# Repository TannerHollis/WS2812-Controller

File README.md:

# WS2812 Controller

 - WS2812 LED: [WS2812](https://cdn-shop.adafruit.com/datasheets/WS2812.pdf)
 - ICE40UL640: [ICE40UL640](https://www.latticesemi.com/~/media/LatticeSemi/Documents/DataSheets/iCE/iCE40UltraLiteDataSheetDS1050.pdf)

## WS2812 LED Controller
[WS2812](https://cdn-shop.adafruit.com/datasheets/WS2812.pdf) LEDs are common RGB LEDs found everywhere today. They are fundamentally controlled by a simple PWM input that signals a single bit in each period. By varying the pwm signal from either 33% duty cycle to 67% duty cycle, one bit after another, data is latched by a timing constraint as seen in the documents. The basic WS2812 RGB LED is shown below.

While in theory, this RGB LED seems practical enough to control. Many various CPU intensive schemes have been created to bit-bang their way to victory. Most methods involve the use of DMA and TIMers with large buffers in STM32 microcontrollers, while in Arduino the method used is usually direct port manipulation and bit-banging. Not to mention other tricks of the trade usually involve using Assembly, *Yuck!* Even with all of the advancements in microcontroller technology of today, it is over-encumbering for the small silicon we all love and play with. 

Ideally there should be little to no overhead in microcontrollers for the actual transmission of the data to the LEDs. Also, there should ideally be on-board storage that will store values of each pixel to offload memory constraints. Well, if you've been looking for something along these lines, then perhaps you should stop and take a look at this project.

## FPGA Based

After looking at the ["smallest FPGA" in the world](https://www.latticesemi.com/Products/FPGAandCPLD/iCE40Ultra), I was curious to check it out for myself. Indeed, it is very small at just 1.4mm x 1.4mm with only 16 pins. In fact, it gets worse at only 10 useable I/O's. But wait, 4 of the 10 I/O's are dedicated SPI port programming lines, leaving you with only 6 I/O's. Oh wait, don't forget that there is only *one* traditional push-pull output and the other 5 are open-drain outputs. The ICE40UL640 also has 640 LUTs (LookUp Tables), and although it's not a good measure to use for capacity in FPGAs, it is a good metric when compared to a basic FGPA like the [Intel Cyclone V-A2](https://www.intel.com/content/dam/www/programmable/us/en/pdfs/literature/hb/cyclone-v/cv_51001.pdf) which has 25,000 LUTs. 

One really great thing about the ICE40UL640 is the RAM included. There are 14 blocks of 512x8bit ram in this FPGA which are 100% utilized for memory. Users can utilize this memory however they want, whether it be for user-data or purely LED data. Each LED requires 24bits of data, which means there is a total capacity of 2389 LEDs in one WS2812 Driver. In fact, this device could be used as additional RAM, which is easy to interface using SPI. Albeit, not the fastest memory controller due to the method of SPI clock detection.

**Below is the Device Architecture**

## SPI 
The SPI module in this device runs off of the device's internal High Frequency Oscillator at 48 MHz. Common practices of SPI communication protocols in FPGAs use clock-domain crossing, which means the internal SPI module operates based on two clocks. Configurations like this tend to operate at higher speeds, but require more logic elements to synthesize. Since this device is so limited in total number of elements, this device uses a "buffer clock" design. Using a buffer of only two clock cycles means, that the effective SPI input clock frequency must be half of the device's operating frequency. For more stable operation, the maximum SPI clock frequency should be:

    f_clk_spi < 24MHz

However, to ensure more stable communications it is recommended to operate well below this frequency when possible.

### SPI Communication Protocol
This device uses 24 bit (3 byte) commands to operate the device, typically consisting of the following format:

    //n'bx = don't care of size n bits
    write =		{3'b100, addr[12:0], data[7:0]};
    read =		{3'b000, addr[12:0], 8'bx};
    clear_ram =	{3'b011, 21'bx};
    fill_ram =	{3'b101, 13'bx, data[7:0]};
    send_leds =	{3'b111, 8'bx, num_leds[12:0]};

There are only a few instructions required to operate this device:
|op|Binary|Hex|Parameter(s)|Description|
|--|--|--|--|--|
|write|100|0x80|addr, data|write data to address|
|read|000|0x00|addr|read data from address|
|clear_ram|011|0x60|N/A|clear ram with zeros|
|fill_ram|101|0xA0|data|fill ram with data|
|send_leds|111|0xE0|num_leds|send leds stopping at num_leds|

A shorthand way of declaring instructions in the c language psuedocode:

    uint8_t op = 0x80;	//write op
    uint16_t addr = 0x1C00;	//maximum address to write to (7168)
    uint8_t data = 0xAA;	//8'b10101010
    
    uint8_t instr[3];	//Sending MSB first
    instr[0] = (addr >> 8) | op; 
	instr[1] = addr;
	instr[2] = data;
	
	GPIO_SetPin(&CS_n, 0);
	SPI_Transmit(&instr, sizeof(instr)); //SPI Transmit set to MSB, CPOL = 0, CPHA = 0
	GPIO_SetPin(&CS_n, 1);
    
**Although this device in hardware is configured for CPOL = 0 and CPHA = 0, future versions might be able to support other SPI transmission configurations.**

## Bus Translator
The "bus translator" in this device is the main state machine responsible for controlling the memory operations as well as preparing the data for the LED Driver module. The bus translator sits idle waiting for a valid instruction to be present. Once it is alerted of a valid instruction, the bus translator will execute the instruction. Both the read and write instructions only take one clock cycle after alerted. 

When the device receives a "send_leds" instruction, since the RAM is only 8 bits wide, the bus translator must prepare data in 3 separate reads before latching the output for the WS2812 module. The WS2812 then will alert the bus translator when new data is required, thus latching the prepared data. This cycle continues until the last chunk of data has been prepared and the LED counter reaches the number of LEDs configured in the "send_leds" instruction. Throughout the duration of sending the LED data, the device will be unresponsive.

The "clear_ram" and "fill_ram" instruction are to provide the user with a quick way to fill the ram with a given value or to quickly clear the values stored in RAM. This process is very fast, because it will execute the entire write operation at the speed of the internal system frequency.

**Bus Translator Device Architecture**

## WS2812 Driver
The LED driver in this device is very simple. It consists of two counters, one for each bit in the 24bit data and one for the bits for the LED. Simply put, when both counters are at zero, the WS2812 module will signal that it needs new RGB data, which latches the input to the module. Upon this output signal, the bus translator will increment the led counter. Since the WS2812  module is in control of the LED counter, the WS2812 will only operate while the "send_leds_n" signal is active low.

To complete the data transmission, the controller must send a reset signal. In the WS2812, the reset signal must be at least 65us.

**This device currently only supports the WS2812 RGB LED, future versions will support other various timing-based RGB LEDs**

## RAM
The one difficulty in this device, the ICE40UL640, is that it [doesn't support tri-states](https://www.latticesemi.com/en/Support/AnswerDatabase/4/7/7/4771). The more normal approach to using a true bus configuration would be to have a single wire connecting to each of the RAM modules "data_out" port. During a read sequence, the unselected RAM modules "data_out" port would be put in high-impedance as to not conflict with the input to the bus translator from the RAM modules. Instead of using a high-impedance state, this device utilizes a demultiplexer (i.e. "demux") that is 8 bitsx16 blocks wide. The input to the demux is a 127 bit wide bus. A selector input to the "demux" will actively change the output of the demux based on which bit of the selector is active.

## TODO

 - [ ] Develop standard C Library for use with microcontrollers
 - [ ] Depending on synthesis size, add programmable LED output settings and more functionality
 - [ ] Finish documenta...

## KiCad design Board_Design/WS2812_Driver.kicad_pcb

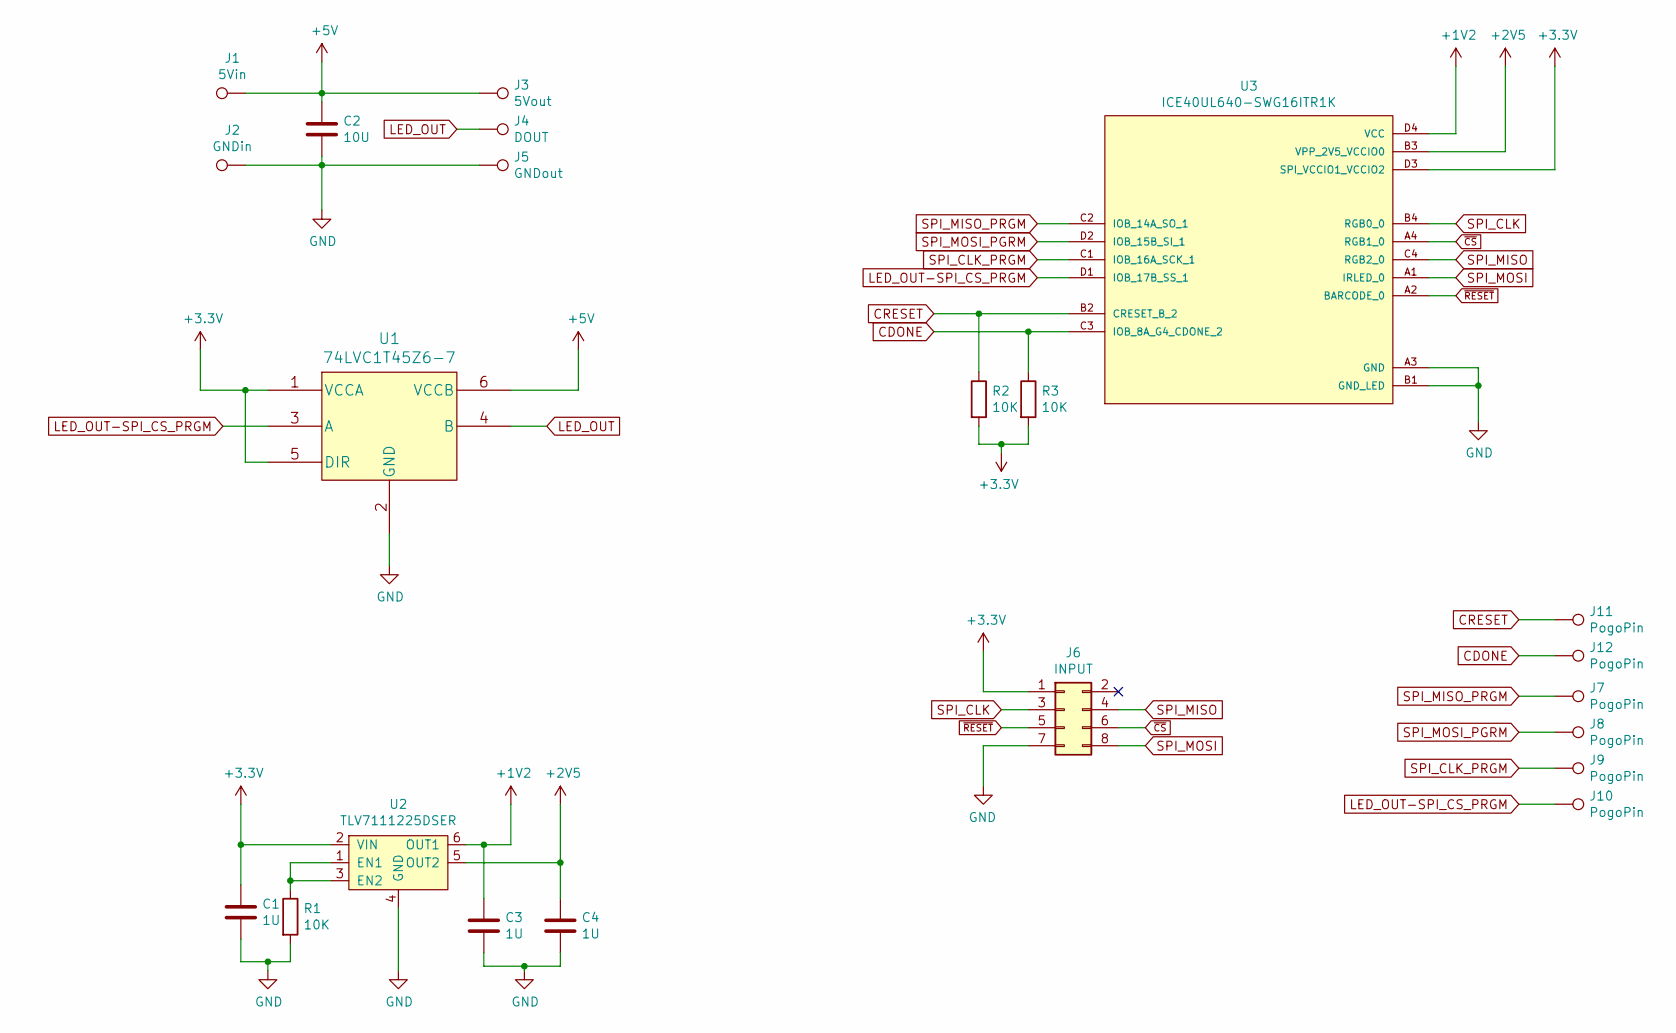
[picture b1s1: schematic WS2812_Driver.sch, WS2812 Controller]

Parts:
C1, C3, C4: 1U; C_0402_1005Metric
C2: 10U; C_0402_1005Metric
J1: 5Vin; TestPoint_THTPad_3.0x3.0mm_Drill1.5mm
J2: GNDin; TestPoint_THTPad_3.0x3.0mm_Drill1.5mm
J3: 5Vout; TestPoint_THTPad_3.0x3.0mm_Drill1.5mm
J4: DOUT; TestPoint_THTPad_3.0x3.0mm_Drill1.5mm
J5: GNDout; TestPoint_THTPad_3.0x3.0mm_Drill1.5mm
J6: INPUT; PinHeader_2x04_P2.54mm_Vertical
J7, J8, J9, J10, J11, J12: PogoPin; TestPoint_Pad_2.0x2.0mm
R1, R2, R3: 10K; R_0402_1005Metric
U1: 74LVC1T45Z6-7
U2: TLV7111225DSER; WSON-6_1.5x1.5mm_P0.5mm
U3: ICE40UL640-SWG16ITR1K; BGA16N35P4X4_140X140X49N

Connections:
+1V2: C3.1, U2.6 (OUT1), U3.D4 (VCC)
+2V5: C4.1, U2.5 (OUT2), U3.B3 (VPP_2V5_VCCIO0)
+3V3: C1.1, J6.1, R2.2, R3.2, U1.1 (VCCA), U1.5 (DIR), U2.2 (VIN), U3.D3 (SPI_VCCIO1_VCCIO2)
+5V: C2.1, J1.1, J3.1, U1.6 (VCCB)
CDONE: J12.1, R3.1, U3.C3 (IOB_8A_G4_CDONE_2)
CRESET: J11.1, R2.1, U3.B2 (CRESET_B_2)
GND: C1.2, C2.2, C3.2, C4.2, J2.1, J5.1, J6.7, R1.2, U1.2 (GND), U2.4 (GND), U3.A3 (GND), U3.B1 (GND_LED)
LED_OUT: J4.1, U1.4 (B)
LED_OUT-SPI_CS_PRGM: J10.1, U1.3 (A), U3.D1 (IOB_17B_SS_1)
unnamed: R1.1, U2.1 (EN1), U2.3 (EN2)
SPI_CLK: J6.3, U3.B4 (RGB0_0)
SPI_CLK_PRGM: J9.1, U3.C1 (IOB_16A_SCK_1)
SPI_MISO: J6.4, U3.C4 (RGB2_0)
SPI_MISO_PRGM: J7.1, U3.C2 (IOB_14A_SO_1)
SPI_MOSI: J6.8, U3.A1 (IRLED_0)
SPI_MOSI_PGRM: J8.1, U3.D2 (IOB_15B_SI_1)
~CS~: J6.6, U3.A4 (RGB1_0)
~RESET~: J6.5, U3.A2 (BARCODE_0)

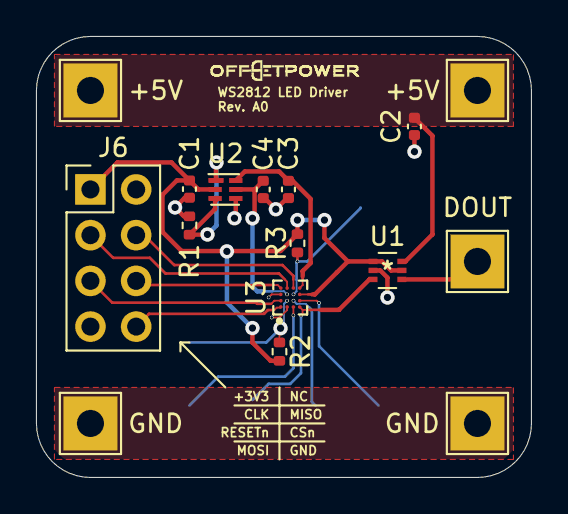
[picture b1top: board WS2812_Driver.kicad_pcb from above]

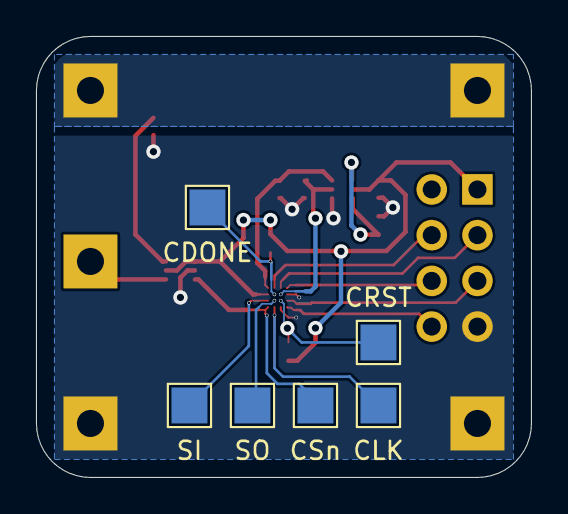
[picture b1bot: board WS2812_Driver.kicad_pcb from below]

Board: 2 copper layers, 27.5 x 24.5 mm, 22 parts (6 on the bottom side), 18 nets.

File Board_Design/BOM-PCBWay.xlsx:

|  |  | WS2812 Driver BOM
Item # | *Designator | *Qty | Manufacturer | *Mfg Part # | Description / Value | *Package/Footprint | Type | Your Instructions / Notes
1 | C1, C3, C4 | 3 | Generic |  | 1U | C_0402_1005Metric | SMD
2 | C2 | 1 | Generic |  | 10U | C_0402_1005Metric | SMD
3 | J1 | 1 |  |  | 5Vin |  | SMD | DNP
4 | J2 | 1 |  |  | GNDin |  | SMD | DNP
5 | J3 | 1 |  |  | 5Vout |  | SMD | DNP
6 | J4 | 1 |  |  | DOUT |  | SMD | DNP
7 | J5 | 1 |  |  | GNDout |  | SMD | DNP
8 | J6 | 1 |  |  | INPUT |  | SMD | DNP
9 | J7, J8, J9, J10, J11, J12 | 6 |  |  | PogoPin |  | SMD | DNP
10 | R1, R2, R3 | 3 | Generic |  | 10K | C_0402_1005Metric | SMD
11 | U1 | 1 | 74LVC1T45Z6-7 | 74LVC1T45Z6-7 | Voltage Level Translator Bidirectional 1 Circuit 1 Channel - SOT-563 | SOT-563 | SMD
12 | U2 | 1 | Texas Instruments | TLV7111225DSER | Linear Voltage Regulator IC Positive Fixed 2 Output 200mA 6-WSON (1.5x1.5) | 6-WSON_1.5mmx1.5mm | SMD
13 | U3 | 1 | Lattice Semiconductor Corporation | ICE40UL640-SWG16ITR1K | series Field Programmable Gate Array (FPGA) IC 10 57344 640 16-XFBGA, WLCSP | 16-XFBGA, WLCSP | SMD
Need a quick and accurante quote? Need an efficient production? Please read SMT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
Click for Instructions on How to Create a BOM

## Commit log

2021-12-06 Initial Commit
    Initial Commit of Rev A0.
2021-12-06 ignore updated
2021-12-06 File deletes
2021-12-07 Device Overview
    Device Overview added. Modified top_tb for simulation. sb_translator has been modified for single-clock read/write operations.
2021-12-07 Added Board Design Files
    3d model + schematic capture
2021-12-07 sb_translator optimizations
    removed a few latched inputs from state machine. sb translator overview changed
2021-12-07 Fixed sb_translator led counter
    erroneously added an additional count to the led counter on the third ram retrieval.
2021-12-07 Implemented LED Driver Type - WIP
    Implemented LED Driver Type, not working for other types other than WS2812
2021-12-07 Uploaded Board Design Files
    Board Design Files have been uploaded
2021-12-07 Folder Organization
    Organized Folder Structure
2021-12-07 Removed excess files
    Removal of spi_tb.v and hf_osc.v files. Not needed for simulation.
2021-12-08 Updated Readme.md
    Updated Readme
2021-12-08 Corrected Image Reference
    Image Reference Corrected in README.md
2021-12-08 Updated the README... again
    Updaed the README file... again
2021-12-08 Corrected formatting.
2021-12-08 Updated for DFR
    Updated design for more design-for-manufacturability.
2021-12-08 File Organization & Instruction
    Organized files for clarity and Added Instructions for Simulation
